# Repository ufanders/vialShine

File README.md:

# vialShine
Here lies a design for a UV LED carrier board to be placed in a small glass vial cap, on a necklace.

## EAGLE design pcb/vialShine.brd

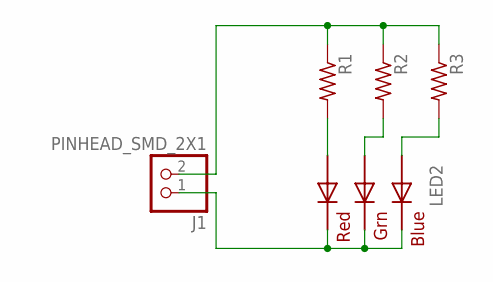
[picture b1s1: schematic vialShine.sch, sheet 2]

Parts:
J1: PINHEAD_SMD_2X1
LED2: RGBLED5050
R1, R2, R3: R-US_R0603; R0603

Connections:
unnamed: LED2.3 (BLUE_A), R3.2
unnamed: J1.2, R1.1, R2.1, R3.1
unnamed: J1.1, LED2.4 (BLUE_C), LED2.5 (RED_C), LED2.6 (GREEN_C)
unnamed: LED2.2 (RED_A), R1.2
unnamed: LED2.1 (GREEN_A), R2.2

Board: 2 copper layers, 5 parts (4 on the bottom side), 5 nets, no tracks yet.

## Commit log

2016-07-19 First commit.
2016-08-12 Added simple 5050 LED and resistors.
